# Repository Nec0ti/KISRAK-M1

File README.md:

# KISRAK-M1 Motor Driver

KISRAK-M1 is a high-efficiency, discrete H-Bridge motor driver designed for micro-robotics. 

## Technical Specifications
- **Type:** Discrete Complementary MOSFET H-Bridge.
- **MOSFETs:** UT2305G (P-Ch) & UTM2054G (N-Ch) logic-level pairs.
- **Logic Level:** 3.3V compatible (Tested with STM32).
- **Protection:** Passive Hardware Dead-Time & Reverse Polarity Protection.

## Passive Dead-Time Design
This project uses an RC-D circuit (47R, 2.2nF, 1N4148) to create asymmetrical switching times, preventing shoot-through without complex MCU PWM dead-time configuration.

## Documentation
For in-depth technical details, design philosophy, and fabrication guides, please refer to the [official documentation](docs/README.md).

## Micromouse Inspiration
To understand the competitive robotics context for which KISRAK-M1 is designed, watch this excellent overview of Micromouse competitions:

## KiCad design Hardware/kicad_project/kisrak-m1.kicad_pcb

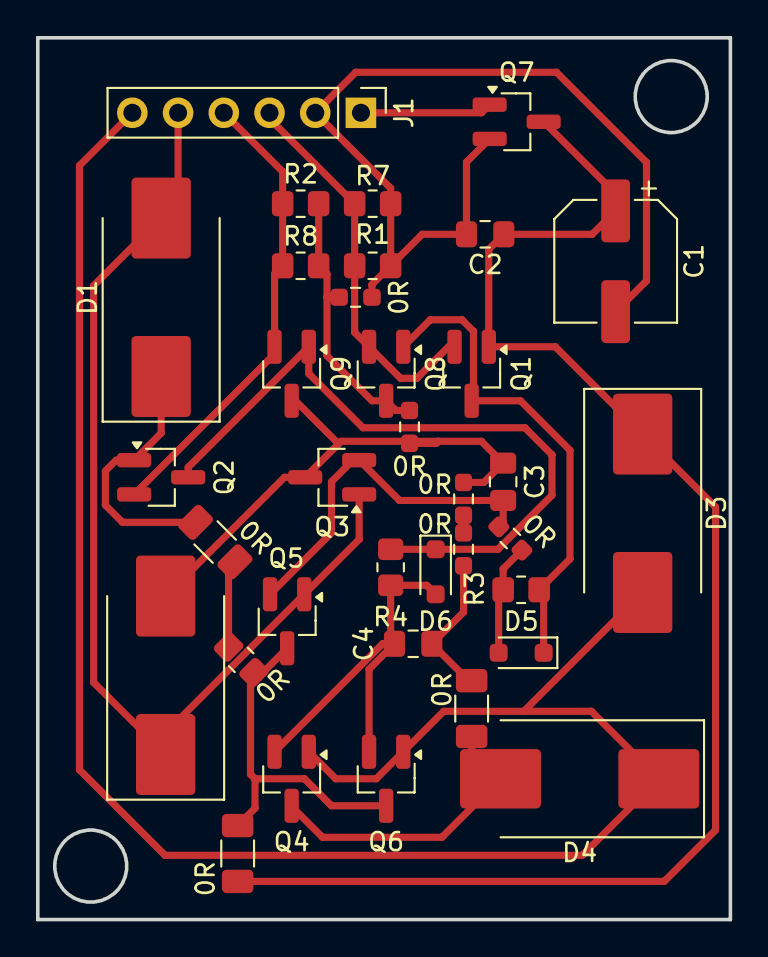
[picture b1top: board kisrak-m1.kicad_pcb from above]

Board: 2 copper layers, 38.5 x 49.0 mm, 35 parts (0 on the bottom side), 11 nets.

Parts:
0R, 0R#6, 0R#7: R_1206_3216Metric_Pad1.30x1.75mm_HandSolder
0R#2, 0R#3, 0R#4, 0R#5, 0R#8: R_0603_1608Metric_Pad0.98x0.95mm_HandSolder
0R#9: R_0805_2012Metric_Pad1.20x1.40mm_HandSolder
C1: 100uF; CP_Elec_6.3x5.2
C2: 100nF; C_0805_2012Metric_Pad1.18x1.45mm_HandSolder
C3, C4: 2.2nF; C_0805_2012Metric_Pad1.18x1.45mm_HandSolder
D1, D2, D3, D4: SS34-HT; D_SMC_Handsoldering
D5, D6: 1N4148WS; D_SOD-323_HandSoldering
J1: PinHeader_1x06_P2.54mm_Vertical
Q1, Q2: MMBT2222A; SOT-23_Handsoldering
Q3, Q4: UTM2054G-AE3-R; SOT-23_Handsoldering
Q5, Q6, Q7: UT2305G-AE3-R; SOT-23_Handsoldering
Q8, Q9: MMBT2907A; SOT-23_Handsoldering
R1, R2: 100k; R_0805_2012Metric_Pad1.20x1.40mm_HandSolder
R3, R4: 47R; R_0805_2012Metric_Pad1.20x1.40mm_HandSolder
R7, R8: 10k; R_0805_2012Metric_Pad1.20x1.40mm_HandSolder

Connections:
/Gate_Left: 0R#8.1, 0R#8.2, C3.1, D5.2 (A), Q3.2 (G), Q5.2 (G), R3.1
/Gate_Right: C4.1, D6.2 (A), Q4.2 (G), Q6.2 (G), R4.1
GND: 0R.1, 0R.2, 0R#2.1, 0R#2.2, 0R#3.1, 0R#3.2, 0R#4.1, 0R#4.2, 0R#5.1, 0R#5.2, C1.2, C2.2, C3.2, C4.2, D2.2 (A), D4.2 (A), J1.2, Q3.3 (S), Q4.3 (S), Q7.2 (G), Q8.3 (E), Q9.3 (E), R1.1, R2.2, R7.1, R8.2
unnamed: D1.2 (A), D2.1 (K), J1.5, Q3.1 (D), Q5.1 (D)
unnamed: D3.2 (A), D4.1 (K), J1.6, Q4.1 (D), Q6.1 (D)
unnamed: D5.1 (K), Q1.3 (E), Q8.1 (C), R3.2
unnamed: D6.1 (K), Q2.3 (E), Q9.1 (C), R4.2
unnamed: J1.1, Q7.1 (D)
unnamed: J1.3, Q1.2 (B), Q8.2 (B), R1.2, R7.2
unnamed: J1.4, Q2.2 (B), Q9.2 (B), R2.1, R8.1
Safe_VCC: 0R#6.1, 0R#6.2, 0R#7.1, 0R#7.2, 0R#9.1, 0R#9.2, C1.1, C2.1, D1.1 (K), D3.1 (K), Q1.1 (C), Q2.1 (C), Q5.3 (S), Q6.3 (S), Q7.3 (S)

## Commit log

2026-05-15 docs: added schematic pdf, etching masks and 3d renders
2026-05-15 feat: added BOM and finalized project structure for documentation
2026-05-15 feat: added detailed documentation
2026-05-15 fix: rename docs
2026-05-15 fix: docs
2026-05-15 update: docs
2026-05-15 docs: update README and restructure documentation to docs/
2026-05-15 docs: add board image to README
